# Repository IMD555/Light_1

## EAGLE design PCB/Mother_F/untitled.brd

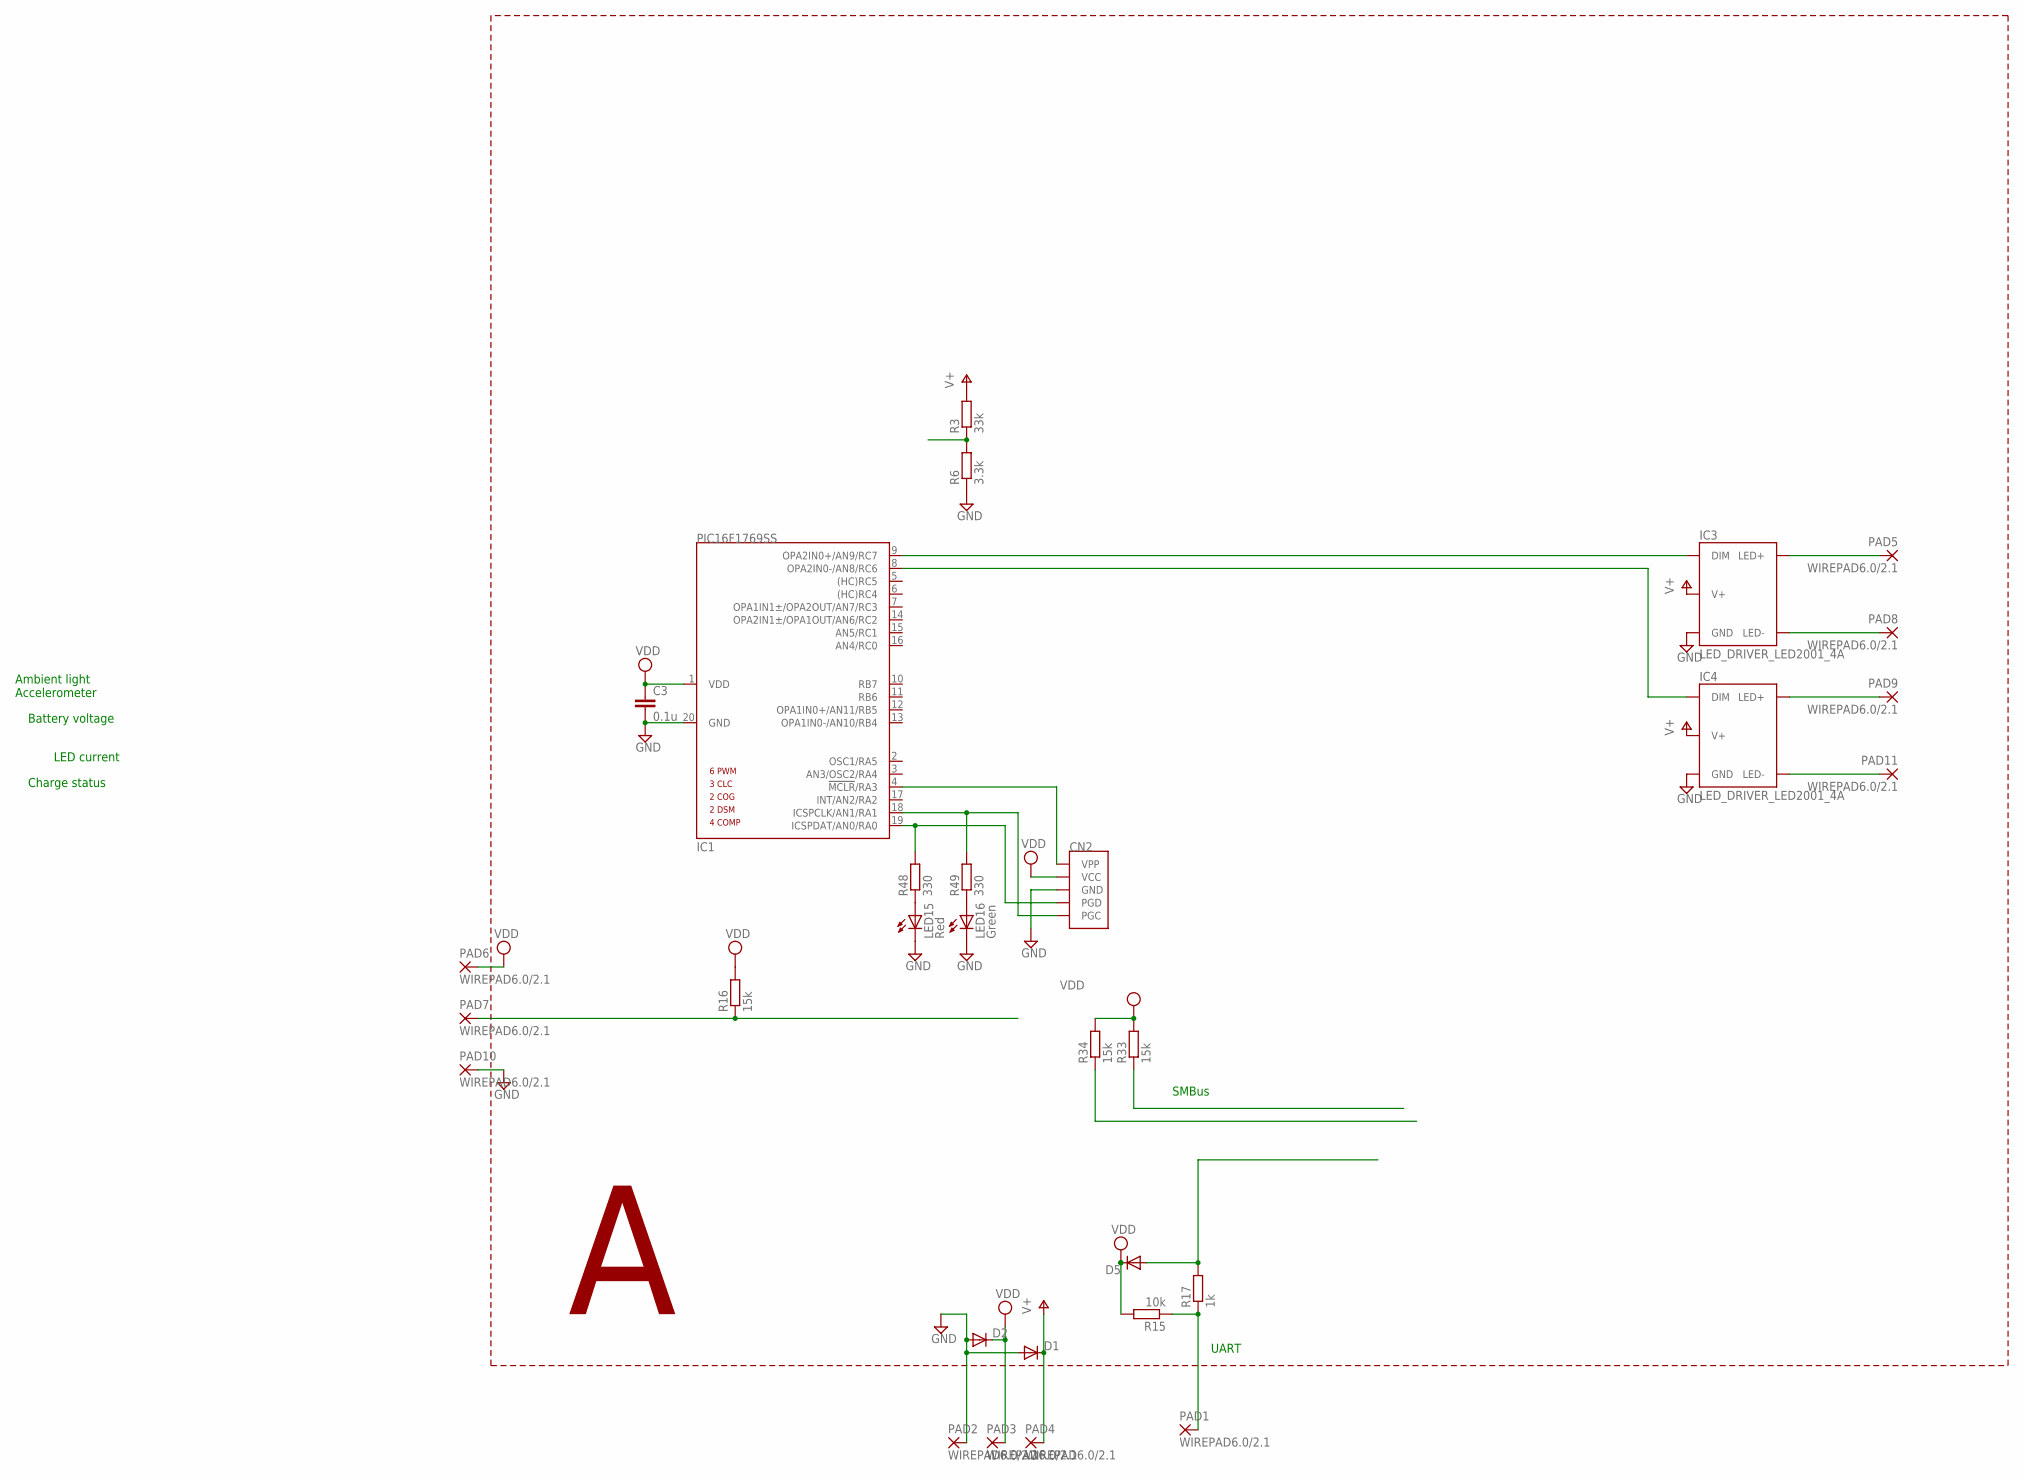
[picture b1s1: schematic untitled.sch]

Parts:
C3: 0.1u; C0402
CN2: ICSPPIN; MINI-ICSP_PIN
D1, D2, D5: DIODE-VMN2; VMN2
IC1: PIC16F1769SS; SSOP20
IC3, IC4: LED_DRIVER_LED2001_4A
LED15: Red; LED3MM
LED16: Green; LED3MM
PAD1, PAD2, PAD3, PAD4, PAD5, PAD6, PAD7, PAD8, PAD9, PAD10, PAD11: WIREPAD6.0/2.1; 6.0/2.1
R3: 33k; R0402
R6: 3.3k; R0402
R15: 10k; R0402
R16, R33, R34: 15k; R0402
R17: 1k; R0402
R48, R49: 330; R0402

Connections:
GND: C3.2, CN2.GND, D1.A, D2.A, IC1.20 (GND), IC3.GND, IC4.GND, LED15.K (C), LED16.K (C), PAD2.1, PAD10.1, R6.1
unnamed: IC3.LED+, PAD5.1
unnamed: IC3.LED-, PAD8.1
unnamed: CN2.VPP, IC1.4 (!MCLR!/RA3)
unnamed: R3.1, R6.2
unnamed: IC4.LED+, PAD9.1
unnamed: IC4.LED-, PAD11.1
unnamed: IC1.9 (OPA2IN0+/AN9/RC7), IC3.DIM
unnamed: IC1.8 (OPA2IN0-/AN8/RC6), IC4.DIM
unnamed: CN2.PGD, IC1.19 (ICSPDAT/AN0/RA0), R48.2
unnamed: CN2.PGC, IC1.18 (ICSPCLK/AN1/RA1), R49.2
unnamed: PAD7.1, R16.1
unnamed: D5.A, R17.2
unnamed: PAD1.1, R15.1, R17.1
unnamed: LED15.A, R48.1
unnamed: LED16.A, R49.1
V+: D1.C, IC3.V+, IC4.V+, PAD4.1, R3.2
VDD: C3.1, CN2.VCC, D2.C, D5.C, IC1.1 (VDD), PAD3.1, PAD6.1, R15.2, R16.2, R33.2, R34.2

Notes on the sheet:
Ambient light Accelerometer
Battery voltage
LED current
Charge status
UART
SMBus

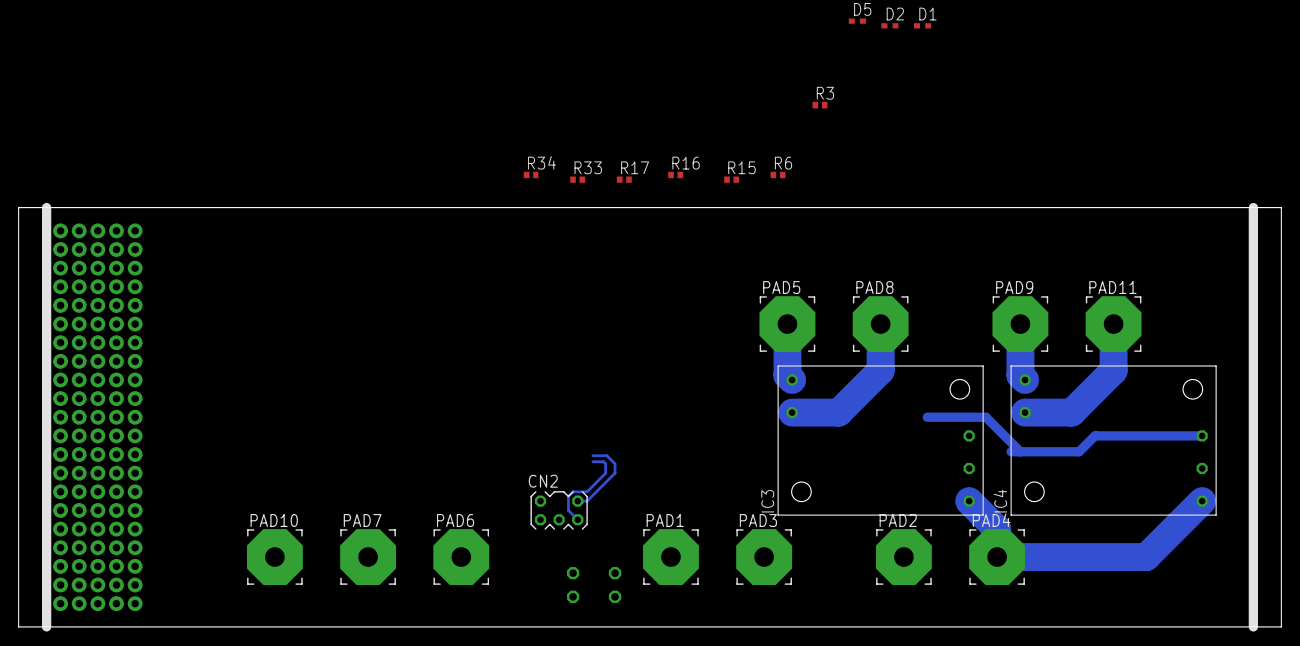
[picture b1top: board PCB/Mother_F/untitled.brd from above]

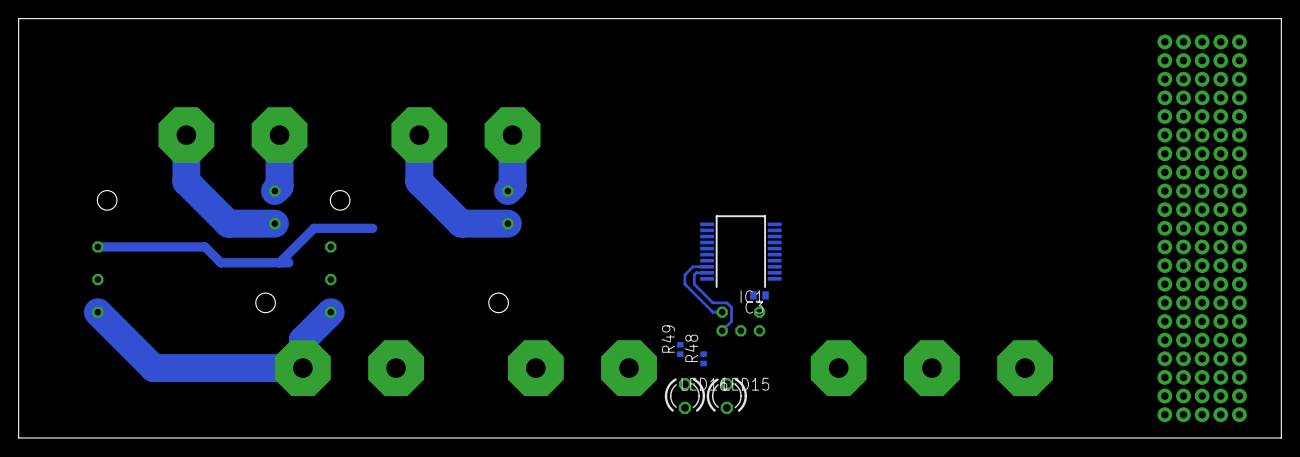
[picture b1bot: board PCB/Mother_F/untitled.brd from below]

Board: 2 copper layers, 135.5 x 45.0 mm, 32 parts (6 on the bottom side), 18 nets.

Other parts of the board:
U$1: RULER
U$2: RULER-S

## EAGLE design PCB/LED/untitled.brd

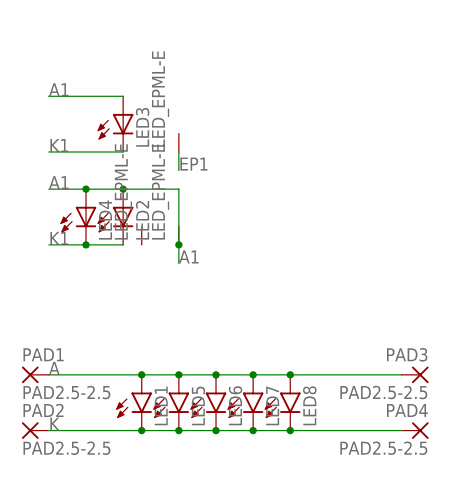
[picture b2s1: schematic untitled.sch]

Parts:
LED1, LED5, LED6, LED7, LED8: LEDSIDELED; OSRAM-SIDELED
LED2, LED3, LED4: LED_EPML-E; ML-E
PAD1, PAD2, PAD3, PAD4: PAD2.5-2.5; SMD2,5-2,5

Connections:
A: LED1.A, LED5.A, LED6.A, LED7.A, LED8.A, PAD1.1, PAD3.1
A1: LED2.A@1 (A), LED2.A@2 (A), LED2.TH (EP), LED3.A@1 (A), LED3.A@2 (A), LED4.A@1 (A), LED4.A@2 (A)
EP1: LED3.TH (EP)
K: LED1.C, LED5.C, LED6.C, LED7.C, LED8.C, PAD2.1, PAD4.1
K1: LED2.C@1 (C), LED2.C@2 (C), LED3.C@1 (C), LED3.C@2 (C), LED4.C@1 (C), LED4.C@2 (C)

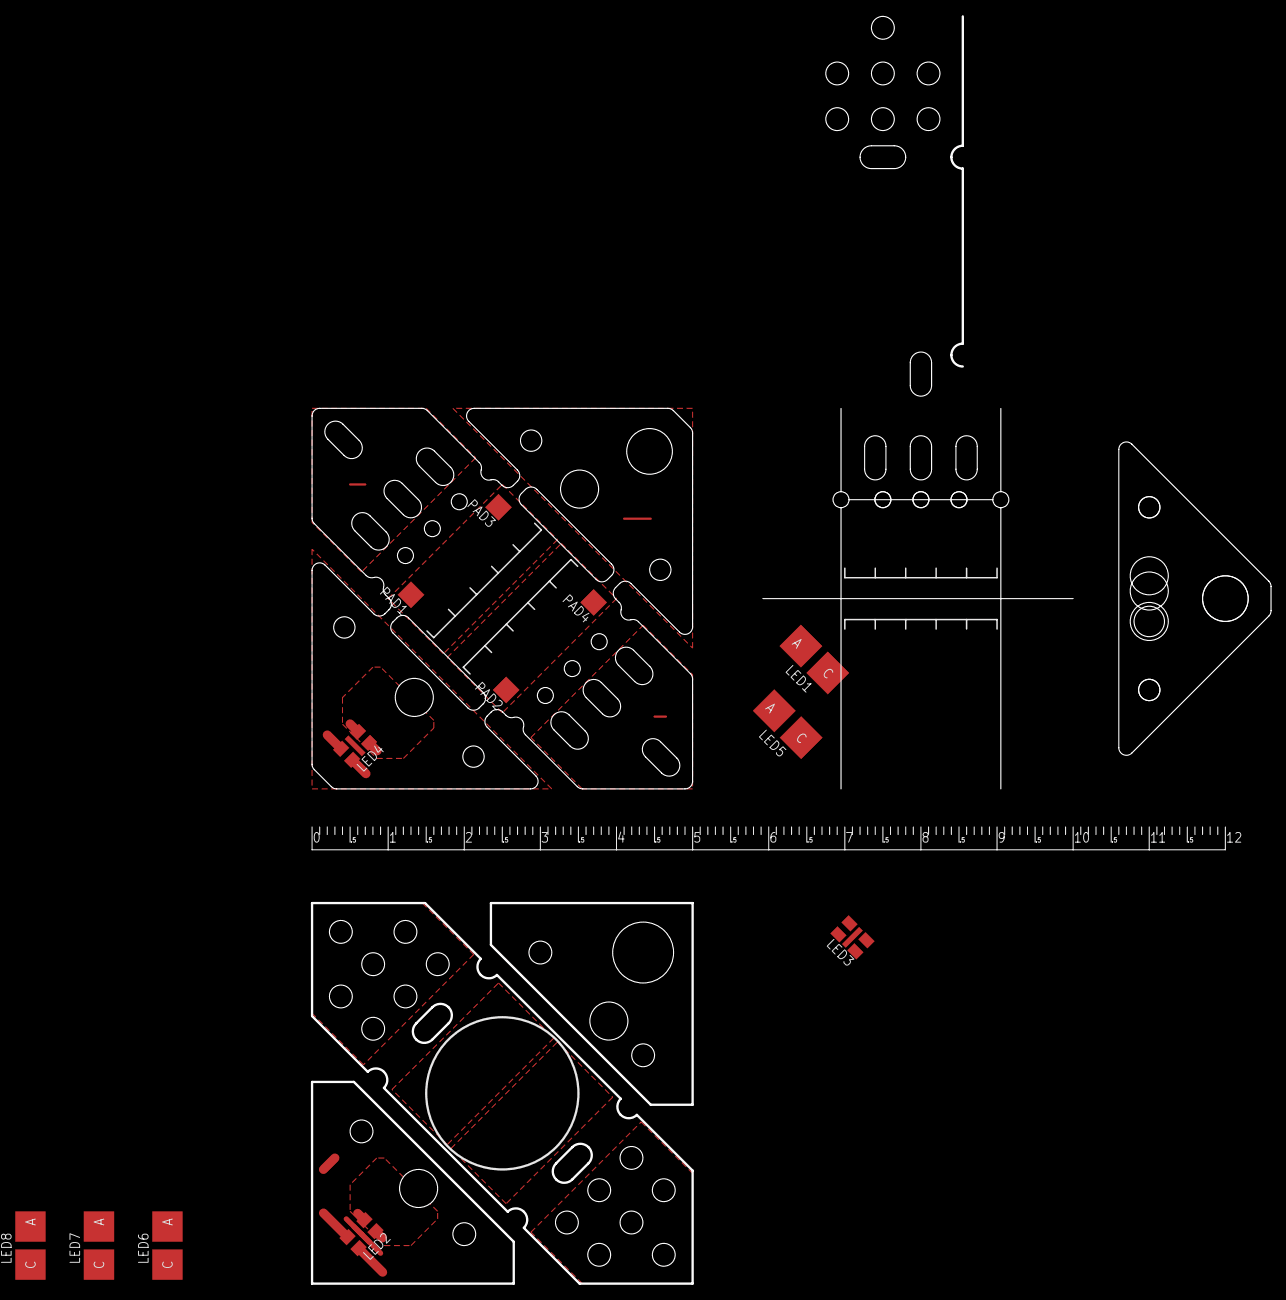
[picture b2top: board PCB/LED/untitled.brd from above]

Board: 2 copper layers, 126.0 x 166.5 mm, 16 parts (0 on the bottom side), 4 nets.

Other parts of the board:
U$1, U$2, U$4: RULER-S
U$3: RULER

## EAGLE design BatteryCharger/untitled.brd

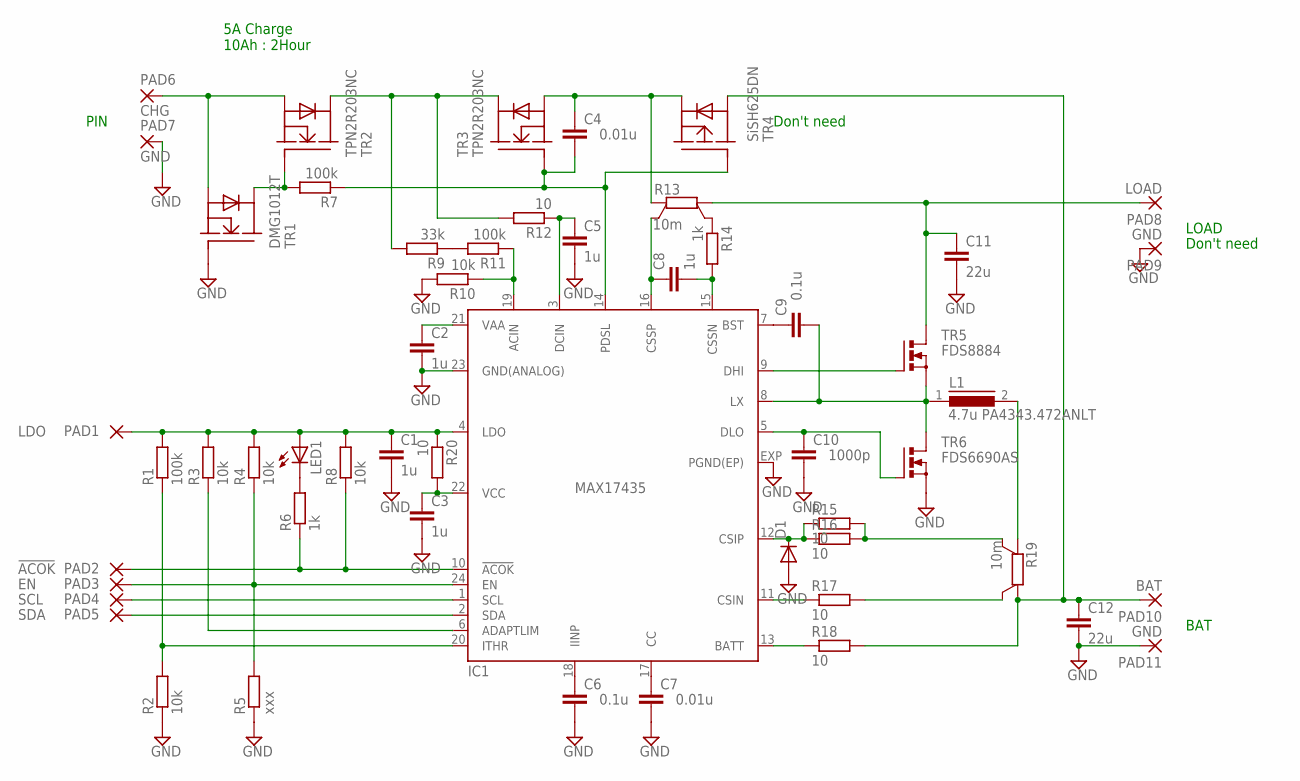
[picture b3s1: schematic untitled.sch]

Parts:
C1, C2, C3, C5, C8: 1u; C0402
C4, C7: 0.01u; C0402
C6, C9: 0.1u; C0402
C10: 1000p; C0402
C11, C12: 22u; C1210
D1: DIODE-VMN2; VMN2
IC1: MAX17435; TQFN24-EP
L1: 4.7u PA4343.472ANLT; DR125
LED1: LED1005; CHIP-LED1005
PAD1: LDO; 2.0/1.3
PAD2: !ACOK; 2.0/1.3
PAD3: EN; 2.0/1.3
PAD4: SCL; 2.0/1.3
PAD5: SDA; 2.0/1.3
PAD6: CHG; 2.0/1.3
PAD7, PAD9, PAD11: GND; 2.0/1.3
PAD8: LOAD; 2.0/1.3
PAD10: BAT; 2.0/1.3
R1, R7, R11: 100k; R0402
R2, R3, R4, R8, R10: 10k; R0402
R5: xxx; R0402
R6, R14: 1k; R0402
R9: 33k; R0402
R12, R15, R16, R17, R18, R20: 10; R0402
R13, R19: 10m; L4T12
TR1: DMG1012T; SOT523
TR2, TR3: TPN2R203NC; TSON_ADVANCE
TR4: SiSH625DN; TSON_ADVANCE
TR5: FDS8884; SO-08
TR6: FDS6690AS; SO-08

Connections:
GND: C1.2, C2.2, C3.2, C5.2, C6.2, C7.2, C10.2, C11.2, C12.2, D1.A, IC1.23 (GND(ANALOG)), IC1.EXP (PGND(EP)), PAD7.1, PAD9.1, PAD11.1, R2.1, R5.1, R10.2, TR1.1 (G), TR6.1 (S), TR6.2 (S), TR6.3 (S)
unnamed: C4.1, R13.B, TR3.1 (S), TR3.2 (S), TR3.3 (S), TR4.1 (S), TR4.2 (S), TR4.3 (S)
unnamed: C8.2, IC1.15 (CSSN), R14.2
unnamed: C8.1, IC1.16 (CSSP), R13.SB
unnamed: D1.C, IC1.12 (CSIP), R15.1, R16.1
unnamed: C11.1, PAD8.1, R13.A, TR5.5 (D), TR5.6 (D), TR5.7 (D), TR5.8 (D)
unnamed: R17.2, R19.SA
unnamed: LED1.C, R6.2
unnamed: R9.1, R11.2
unnamed: R13.SA, R14.1
unnamed: C3.1, IC1.22 (VCC), R20.2
unnamed: C9.1, IC1.7 (BST)
unnamed: R9.2, R12.2, TR2.5 (D), TR2.5_ (D), TR2.6 (D), TR2.7 (D), TR2.8 (D), TR2.8_ (D), TR2.EP (D), TR2.EP2 (D), TR3.5 (D), TR3.5_ (D), TR3.6 (D), TR3.7 (D), TR3.8 (D), TR3.8_ (D), TR3.EP (D), TR3.EP2 (D)
unnamed: C9.2, IC1.8 (LX), L1.1, TR5.1 (S), TR5.2 (S), TR5.3 (S), TR6.5 (D), TR6.6 (D), TR6.7 (D), TR6.8 (D)
unnamed: L1.2, R19.B
unnamed: R7.2, TR1.3 (D), TR2.4 (G)
unnamed: C12.1, PAD10.1, R18.2, R19.A, TR4.5 (D), TR4.5_ (D), TR4.6 (D), TR4.7 (D), TR4.8 (D), TR4.8_ (D), TR4.EP (D), TR4.EP2 (D)
unnamed: R15.2, R16.2, R19.SB
unnamed: IC1.11 (CSIN), R17.1
unnamed: IC1.13 (BATT), R18.1
unnamed: C6.1, IC1.18 (IINP)
unnamed: C7.1, IC1.17 (CC)
unnamed: IC1.20 (ITHR), R1.1, R2.2
unnamed: C1.1, IC1.4 (LDO), LED1.A, PAD1.1, R1.2, R3.2, R4.2, R8.2, R20.1
unnamed: C2.1, IC1.21 (VAA)
unnamed: IC1.24 (EN), PAD3.1, R4.1, R5.2
unnamed: IC1.10 (!ACOK), PAD2.1, R6.1, R8.1
unnamed: IC1.6 (ADAPTLIM), R3.1
unnamed: IC1.9 (DHI), TR5.4 (G)
unnamed: C10.1, IC1.5 (DLO), TR6.4 (G)
unnamed: IC1.1 (SCL), PAD4.1
unnamed: IC1.2 (SDA), PAD5.1
unnamed: C5.1, IC1.3 (DCIN), R12.1
unnamed: IC1.19 (ACIN), R10.1, R11.1
unnamed: C4.2, IC1.14 (PDSL), R7.1, TR3.4 (G), TR4.4 (G)
unnamed: PAD6.1, TR1.2 (S), TR2.1 (S), TR2.2 (S), TR2.3 (S)

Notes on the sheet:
BAT
LOAD
PIN
5A Charge 10Ah : 2Hour
Don't need

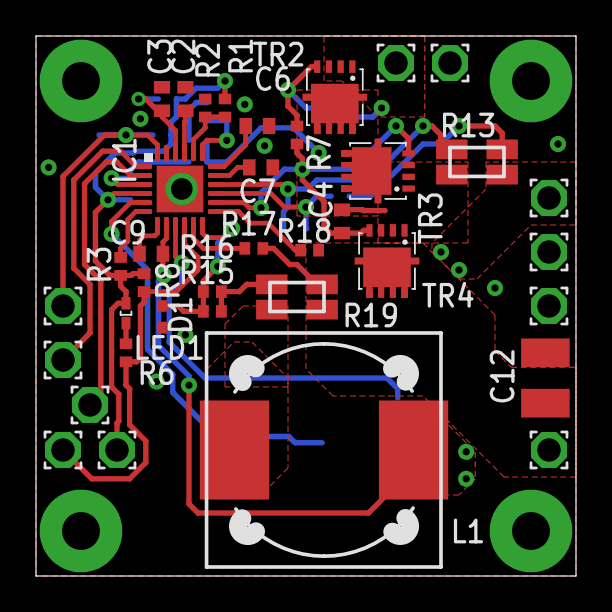
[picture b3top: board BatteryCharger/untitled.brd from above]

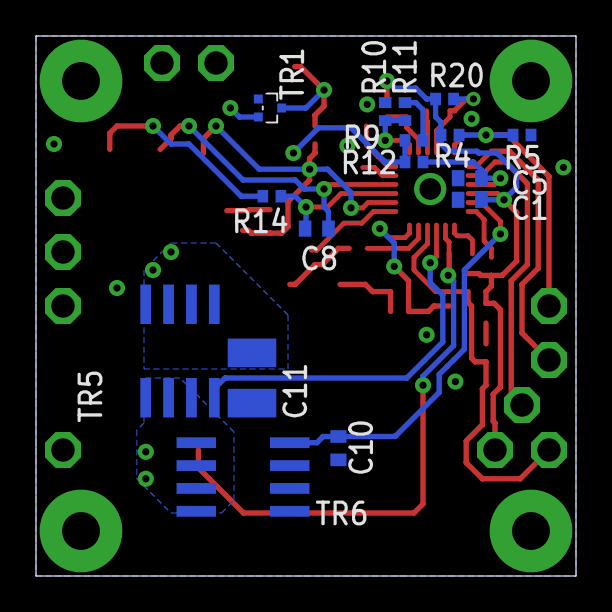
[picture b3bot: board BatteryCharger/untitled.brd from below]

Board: 2 copper layers, 30.0 x 30.0 mm, 53 parts (16 on the bottom side), 36 nets.

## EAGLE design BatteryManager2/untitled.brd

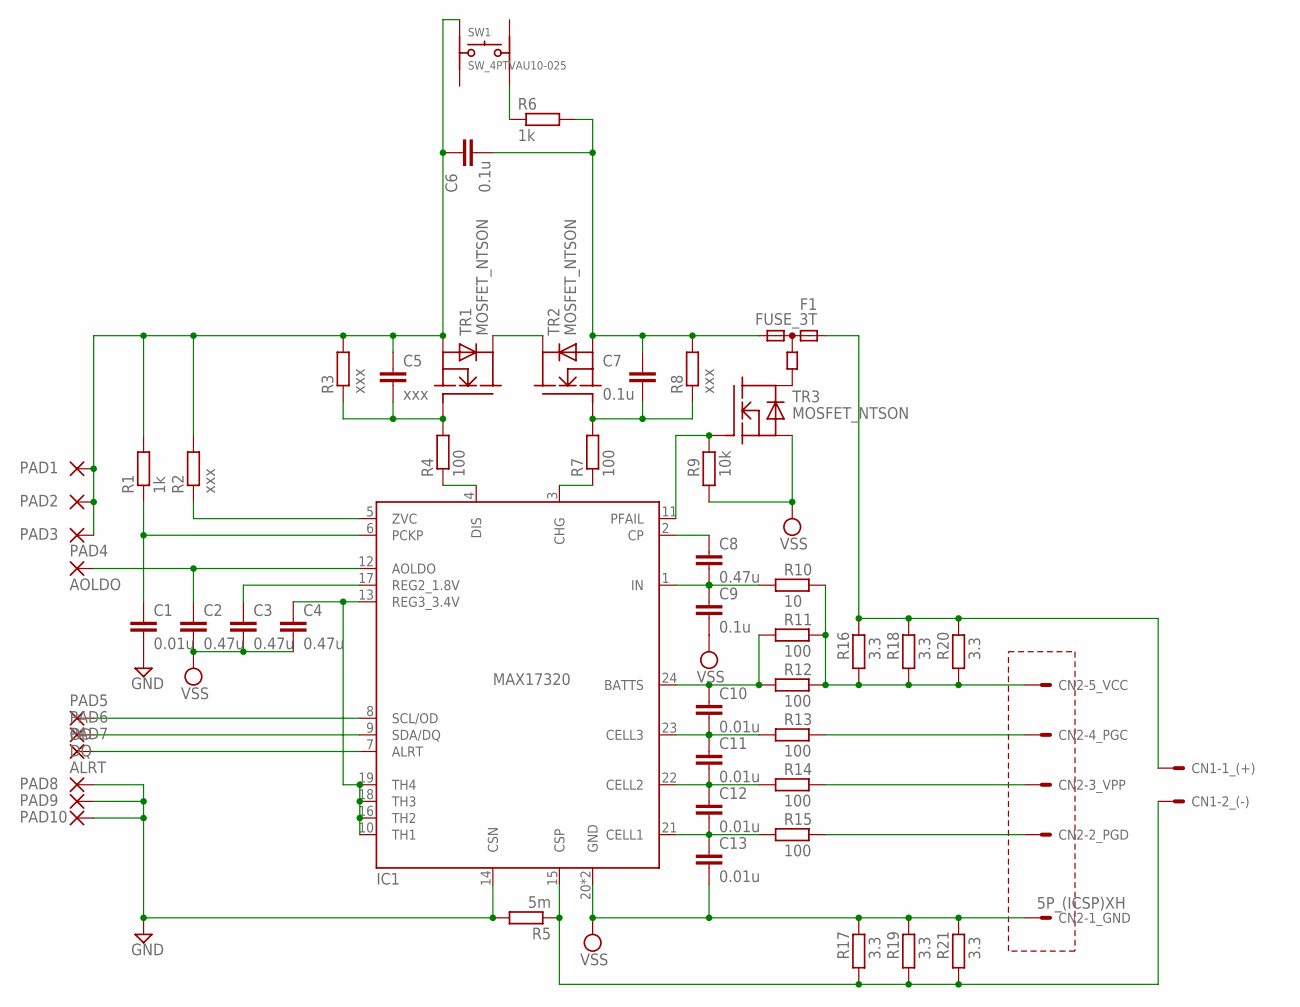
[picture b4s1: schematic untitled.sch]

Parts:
C1, C10, C11, C12, C13: 0.01u; C0402
C2, C3, C4, C8: 0.47u; C0402
C5: xxx; C0402
C6, C7, C9: 0.1u; C0402
CN1: 2P_(POWER)VH; VH-2
CN2: 5P_(ICSP)XH; XH-5
F1: FUSE_3T; FUSE_ITV4030
IC1: MAX17320; TQFN24-EP
PAD1, PAD2, PAD3, PAD8, PAD9, PAD10: WIREPAD2.0/1.2; 2.0/1.3
PAD4: AOLDO; 2.0/1.3
PAD5: OD; 2.0/1.3
PAD6: DQ; 2.0/1.3
PAD7: ALRT; 2.0/1.3
R1, R6: 1k; R0402
R2, R3, R8: xxx; R0402
R4, R7, R11, R12, R13, R14, R15: 100; R0402
R5: 5m; R1210
R9: 10k; R0402
R10: 10; R0402
R16, R17, R18, R19, R20, R21: 3.3; R0402
SW1: SW_4PTVAU10-025; TVAU10-025
TR1, TR2, TR3: MOSFET_NTSON; TSON_ADVANCE

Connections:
GND: C1.2, IC1.14 (CSN), PAD8.1, PAD9.1, PAD10.1, R5.2
unnamed: CN2.4, R15.2
unnamed: IC1.11 (PFAIL), R9.2, TR3.4 (G)
unnamed: C8.1, IC1.2 (CP)
unnamed: CN2.3, R14.2
unnamed: C6.2, C7.1, F1.F2, R6.2, R8.2, TR2.1 (S), TR2.2 (S), TR2.3 (S)
unnamed: CN2.1, R10.2, R11.2, R12.2, R16.1, R18.1, R20.1
unnamed: CN2.2, R13.2
unnamed: C2.1, IC1.12 (AOLDO), PAD4.1
unnamed: IC1.3 (CHG), R7.1
unnamed: CN1.1, F1.F1, R16.2, R18.2, R20.2
unnamed: TR1.5 (D), TR1.5_ (D), TR1.6 (D), TR1.7 (D), TR1.8 (D), TR1.8_ (D), TR1.EP (D), TR1.EP2 (D), TR2.5 (D), TR2.5_ (D), TR2.6 (D), TR2.7 (D), TR2.8 (D), TR2.8_ (D), TR2.EP (D), TR2.EP2 (D)
unnamed: IC1.4 (DIS), R4.1
unnamed: C8.2, C9.1, IC1.1 (IN), R10.1
unnamed: C4.1, IC1.10 (TH1), IC1.13 (REG3_3.4V), IC1.16 (TH2), IC1.18 (TH3), IC1.19 (TH4)
unnamed: F1.H, TR3.5 (D), TR3.5_ (D), TR3.6 (D), TR3.7 (D), TR3.8 (D), TR3.8_ (D), TR3.EP (D), TR3.EP2 (D)
unnamed: CN1.2, IC1.15 (CSP), R5.1, R17.1, R19.1, R21.1
unnamed: C3.1, IC1.17 (REG2_1.8V)
unnamed: IC1.5 (ZVC), R2.1
unnamed: C7.2, R7.2, R8.1, TR2.4 (G)
unnamed: C1.1, IC1.6 (PCKP), R1.1
unnamed: C5.2, R3.1, R4.2, TR1.4 (G)
unnamed: C5.1, C6.1, PAD1.1, PAD2.1, PAD3.1, R1.2, R2.2, R3.2, SW1.P$1 (A), TR1.1 (S), TR1.2 (S), TR1.3 (S)
unnamed: IC1.8 (SCL/OD), PAD5.1
unnamed: IC1.9 (SDA/DQ), PAD6.1
unnamed: C10.2, C11.1, IC1.23 (CELL3), R13.1
unnamed: IC1.7 (ALRT), PAD7.1
unnamed: R6.1, SW1.P$4 (=B)
unnamed: C11.2, C12.1, IC1.22 (CELL2), R14.1
unnamed: C12.2, C13.1, IC1.21 (CELL1), R15.1
unnamed: C10.1, IC1.24 (BATTS), R11.1, R12.1
VSS: C2.2, C3.2, C4.2, C9.2, C13.2, CN2.5, IC1.20 (GND), IC1.EXP (GND), R9.1, R17.2, R19.2, R21.2, TR3.1 (S), TR3.2 (S), TR3.3 (S)

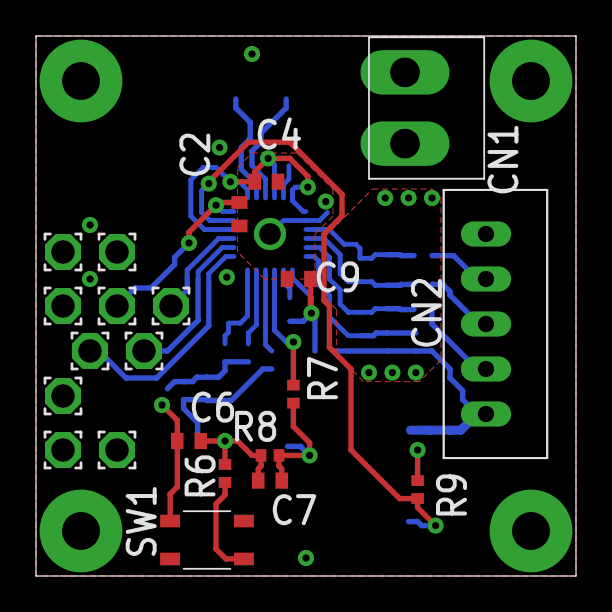
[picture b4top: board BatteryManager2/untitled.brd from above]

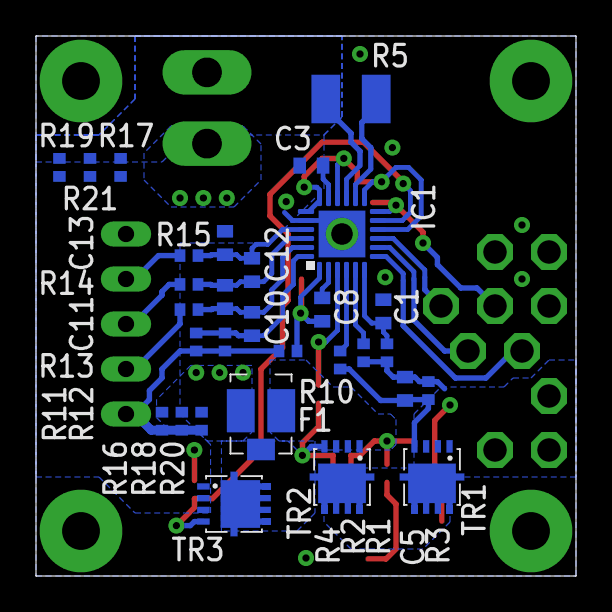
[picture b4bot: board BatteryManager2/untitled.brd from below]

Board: 2 copper layers, 30.0 x 30.0 mm, 52 parts (30 on the bottom side), 32 nets.

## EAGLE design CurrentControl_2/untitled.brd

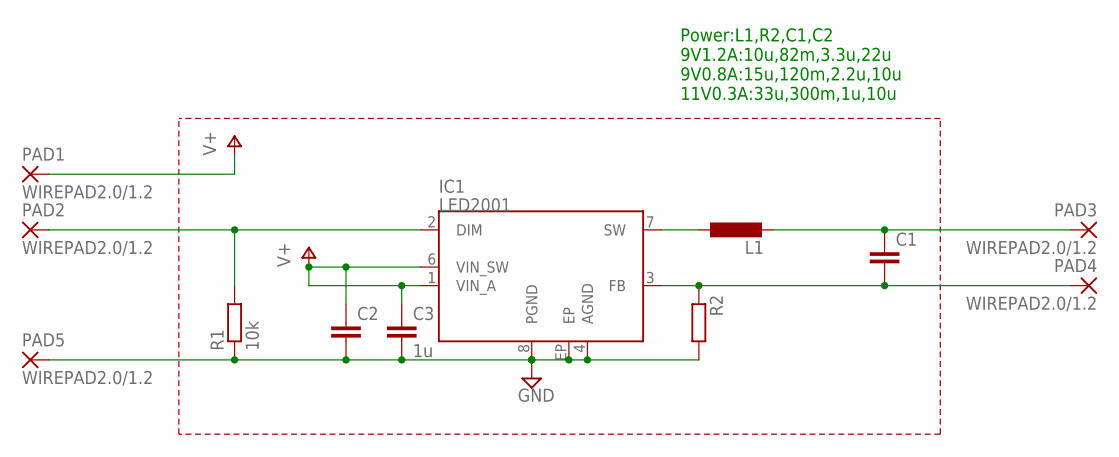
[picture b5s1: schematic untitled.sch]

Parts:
C1: C-EUC1210; C1210
C2: C-EUC0805; C0805
C3: 1u; C0603
IC1: LED2001; HSOP8
L1: L-EUL8080; L8080
PAD1, PAD2, PAD3, PAD4, PAD5: WIREPAD2.0/1.2; 2.0/1.3
R1: 10k; R0402
R2: R-EU_R1210; R1210

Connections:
GND: C2.2, C3.2, IC1.4 (AGND), IC1.8 (PGND), IC1.EP, PAD5.1, R1.1, R2.2
unnamed: IC1.7 (SW), L1.1
unnamed: C1.1, L1.2, PAD3.1
unnamed: C1.2, IC1.3 (FB), PAD4.1, R2.1
unnamed: IC1.2 (DIM), PAD2.1, R1.2
V+: C2.1, C3.1, IC1.1 (VIN_A), IC1.6 (VIN_SW), PAD1.1

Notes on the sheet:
Power:L1,R2,C1,C2 9V1.2A:10u,82m,3.3u,22u 9V0.8A:15u,120m,2.2u,10u 11V0.3A:33u,300m,1u,10u

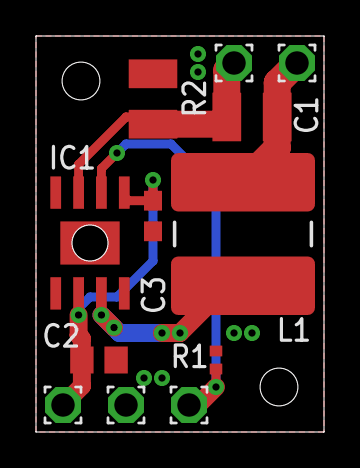
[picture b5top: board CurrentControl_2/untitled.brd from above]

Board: 2 copper layers, 16.0 x 22.0 mm, 12 parts (0 on the bottom side), 6 nets.

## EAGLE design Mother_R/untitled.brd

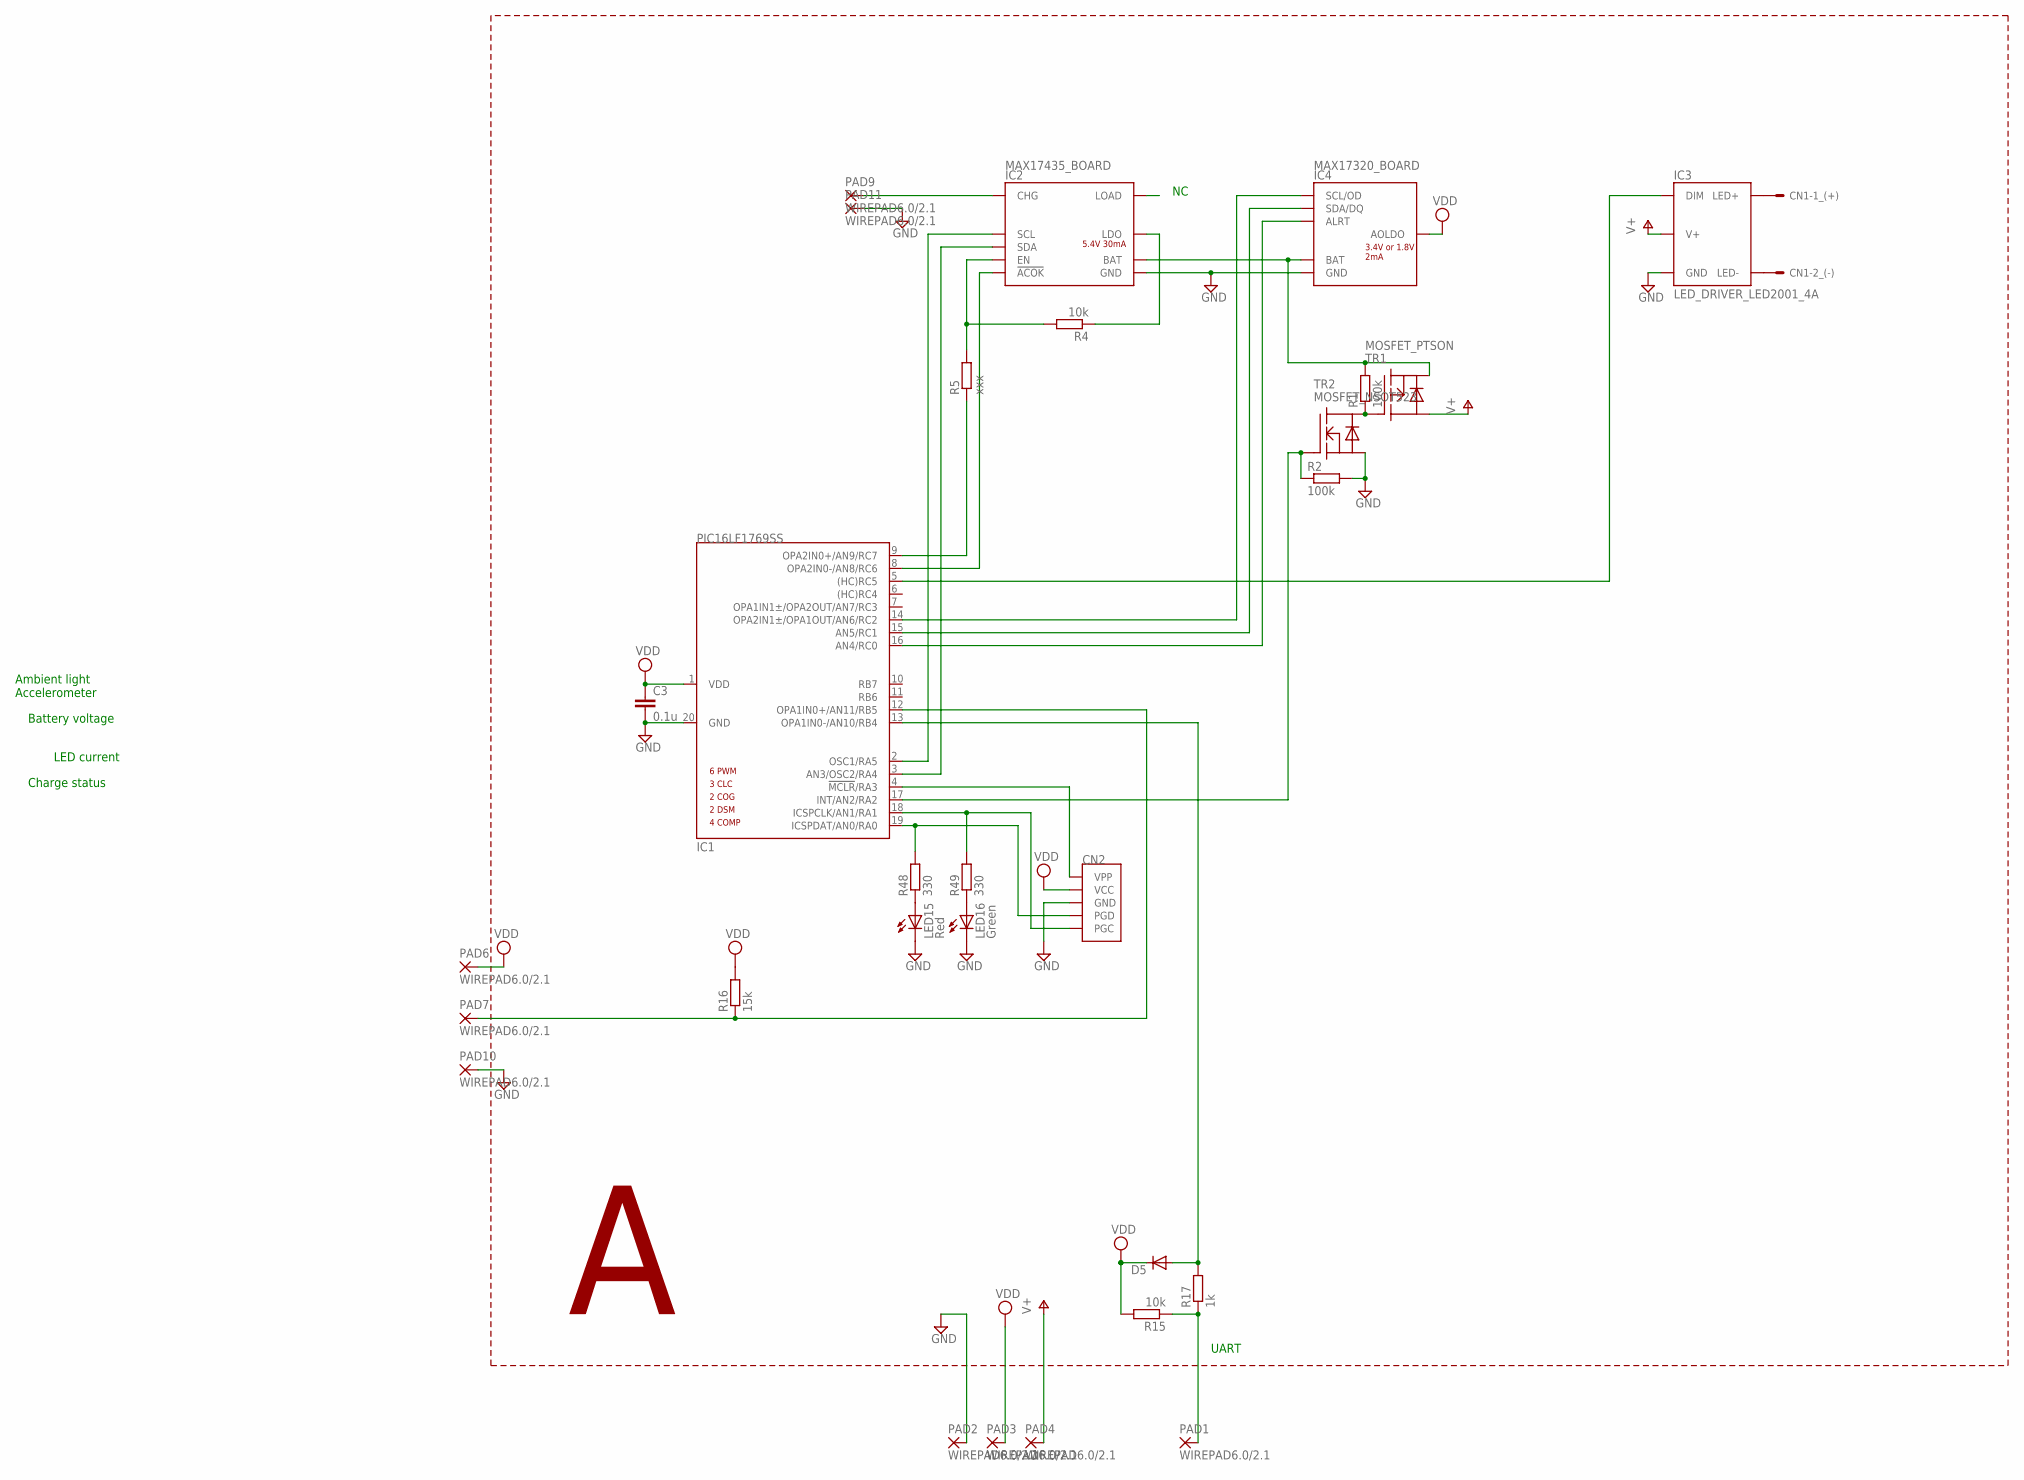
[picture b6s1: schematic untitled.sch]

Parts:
C3: 0.1u; C0402
CN1: 2P_(POWER)XH_S; XH-2_S
CN2: ICSPEDGE; MINI-ICSP_EDGE
D5: DIODE-VMN2; VMN2
IC1: PIC16LF1769SS; SSOP20
IC2: MAX17435_BOARD
IC3: LED_DRIVER_LED2001_4A
IC4: MAX17320_BOARD
LED15: Red; CHIP-LED1606(SIDE)
LED16: Green; CHIP-LED1606(SIDE)
PAD1, PAD2, PAD3, PAD4, PAD6, PAD7, PAD9, PAD10, PAD11: WIREPAD6.0/2.1; 6.0/2.1
R1, R2: 100k; R0402
R4, R15: 10k; R0402
R5: xxx; R0402
R16: 15k; R0402
R17: 1k; R0402
R48, R49: 330; R0402
TR1: MOSFET_PTSON; TSON_ADVANCE
TR2: MOSFET_NSOT523; SOT523

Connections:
GND: C3.2, CN2.GND, IC1.20 (GND), IC2.GND, IC2.GND@1 (GND), IC2.GND@2 (GND), IC2.GND@3 (GND), IC2.GND@4 (GND), IC2.GND@5 (GND), IC2.GND@6 (GND), IC3.GND, IC3.GND@1 (GND), IC3.GND@2 (GND), IC4.GND, IC4.GND@1 (GND), IC4.GND@2 (GND), IC4.GND@3 (GND), IC4.GND@4 (GND), IC4.GND@5 (GND), IC4.GND@6 (GND), LED15.C, LED16.C, PAD2.1, PAD10.1, PAD11.1, R2.2, TR2.2 (S)
unnamed: CN1.1, IC3.LED+
unnamed: CN1.2, IC3.LED-
unnamed: CN2.VPP, IC1.4 (!MCLR!/RA3)
unnamed: IC2.CHG, PAD9.1
unnamed: IC1.5 ((HC)RC5), IC3.DIM
unnamed: IC2.BAT, IC4.BAT, IC4.BAT@1 (BAT), IC4.BAT@2 (BAT), R1.2, TR1.1 (S), TR1.2 (S), TR1.3 (S)
unnamed: IC1.2 (OSC1/RA5), IC2.SCL
unnamed: IC1.9 (OPA2IN0+/AN9/RC7), R5.1
unnamed: IC1.8 (OPA2IN0-/AN8/RC6), IC2.!ACOK
unnamed: IC1.3 (AN3/OSC2/RA4), IC2.SDA
unnamed: R1.1, TR1.4 (G), TR2.3 (D)
unnamed: CN2.PGD, IC1.19 (ICSPDAT/AN0/RA0), R48.2
unnamed: IC1.17 (INT/AN2/RA2), R2.1, TR2.1 (G)
unnamed: CN2.PGC, IC1.18 (ICSPCLK/AN1/RA1), R49.2
unnamed: IC2.LDO, R4.1
unnamed: IC1.15 (AN5/RC1), IC4.SDA/DQ
unnamed: IC1.16 (AN4/RC0), IC4.ALRT
unnamed: IC1.14 (OPA2IN1±/OPA1OUT/AN6/RC2), IC4.SCL/OD
unnamed: IC2.EN, R4.2, R5.2
unnamed: D5.A, IC1.13 (OPA1IN0-/AN10/RB4), R17.2
unnamed: IC1.12 (OPA1IN0+/AN11/RB5), PAD7.1, R16.1
unnamed: PAD1.1, R15.1, R17.1
unnamed: LED15.A, R48.1
unnamed: LED16.A, R49.1
V+: IC3.V+, PAD4.1, TR1.5 (D), TR1.5_ (D), TR1.6 (D), TR1.7 (D), TR1.8 (D), TR1.8_ (D), TR1.EP (D), TR1.EP2 (D)
VDD: C3.1, CN2.VCC, D5.C, IC1.1 (VDD), IC4.AOLDO, PAD3.1, PAD6.1, R15.2, R16.2

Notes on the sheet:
Ambient light Accelerometer
Battery voltage
LED current
Charge status
UART

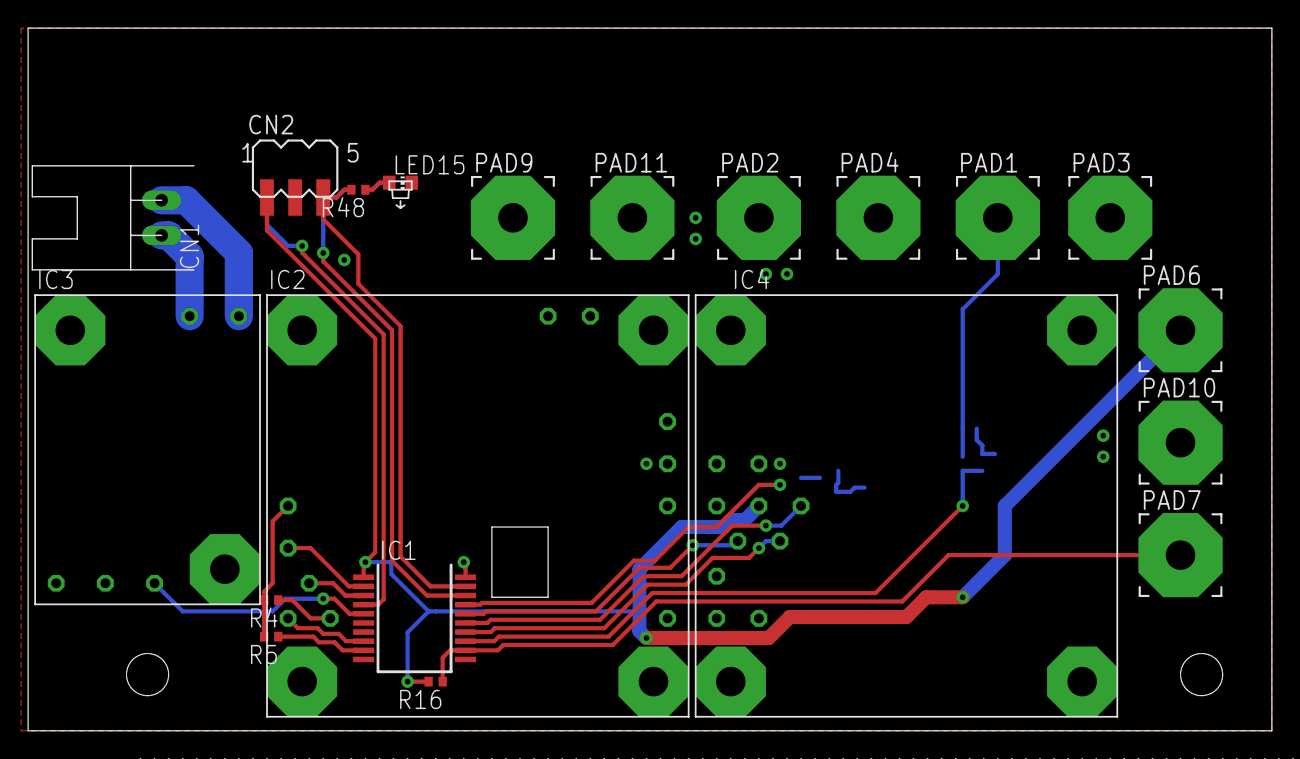
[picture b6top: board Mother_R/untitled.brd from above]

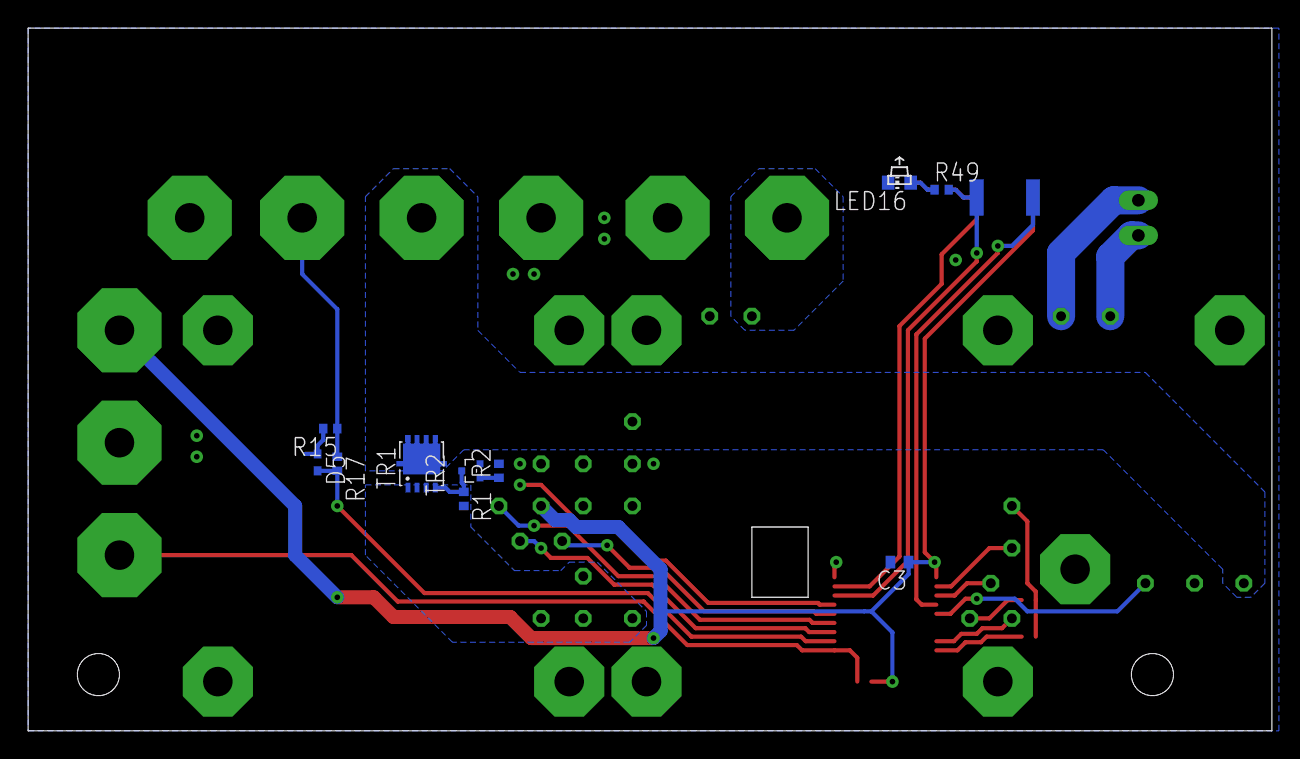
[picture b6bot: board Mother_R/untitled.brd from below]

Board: 2 copper layers, 88.5 x 50.0 mm, 32 parts (10 on the bottom side), 27 nets.

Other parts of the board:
U$1: RULER
U$2: RULER-S
